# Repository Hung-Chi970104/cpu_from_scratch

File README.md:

## Hardware Specifications & Bill of Materials (BOM)
*** Sry this board is still in production but I'll reship it once it's delivered!!!

This project is inspired by Hyperspace Pirate: https://youtu.be/X31B1pVow1o?si=pDOqtu37fK6EBQ2z

This DIY 4-but CPU uses BJT logic to build various logic gates, while using discrete NPN transistors as saturated switches

| Component Class | Specification / Part Number | Function |
| --- | --- | --- |
| **Active Switching** | 2N3904 (NPN BJT) | Core logic gates (amplification and switching) |
| **Passive Routing** | Standard Rectifier Diodes | Signal isolation and OR-tie routing |
| **Pull-up/Pull-down** | 10kΩ Resistors | Ensuring definitive HIGH/LOW logic states |
| **Base Biasing** | 4.7kΩ Resistors | Base current limiting to prevent thermal runaway |
| **Current Limiting** | 1kΩ Resistors | Collector current limiting |

---

## Schematic Design

The architecture has both **SUM** and **CARRY (Cout)** logic using fundamental logic gates built from scratch

### Logic Gate Topologies

The computational core relies on three primary gate topologies designed from discrete NPN transistors:

1. **NAND Gate:** Series-connected BJTs requiring all inputs to be HIGH to pull the output LOW
2. **NOR Gate:** Parallel-connected BJTs where any HIGH input pulls the output LOW
3. **XOR Gate:** A composite gate critical for the SUM generation

*Gate Implementation Reference:*

* [XOR Gate Schematic](https://github.com/user-attachments/assets/9e057bf3-4b33-4ee1-a783-3fd075c37234)
* [NOR Gate Schematic](https://github.com/user-attachments/assets/835cebbe-9da9-4931-9af1-0fc856e21aca)
* [NAND Gate Schematic](https://github.com/user-attachments/assets/38a2fae2-0add-45c0-82a7-d2f594ea8222)

---

## Validation Using Truth Table

The circuit has been validated against the standard 1-bit full adder truth table, successfully transitioning between all 8 states cleanly:

| Input A | Input B | Carry In (Cin) | SUM Output | Carry Out (Cout) |
| --- | --- | --- | --- | --- |
| 0 | 0 | 0 | **0** | **0** |
| 0 | 0 | 1 | **1** | **0** |
| 0 | 1 | 0 | **1** | **0** |
| 0 | 1 | 1 | **0** | **1** |
| 1 | 0 | 0 | **1** | **0** |
| 1 | 0 | 1 | **0** | **1** |
| 1 | 1 | 0 | **0** | **1** |
| 1 | 1 | 1 | **1** | **1** |

---

## Technical Challenges

To build this, I was forced to learn many things that I hadn't even seen before, such as truth table and logic gates. Truth table is the foundation of computing logic, while logic gates are the way to implement the the logic

* **Fan-Out Limitations & Signal Integrity:** Driving multiple inputs from a single output stage caused severe voltage drops. This required very careful pull-up and base resistor values to ensure subsequent transistor stages have adequate saturation current without dragging the logic HIGH state into the regions that should be low
* **XOR Current Starvation:** The initial Exclusive-OR (XOR) architecture failed due to a topology that tried to drive two separate transistor bases from a single unbuffered node. And this caused current to split in two parallel streams, preventing either transistor from fully switching

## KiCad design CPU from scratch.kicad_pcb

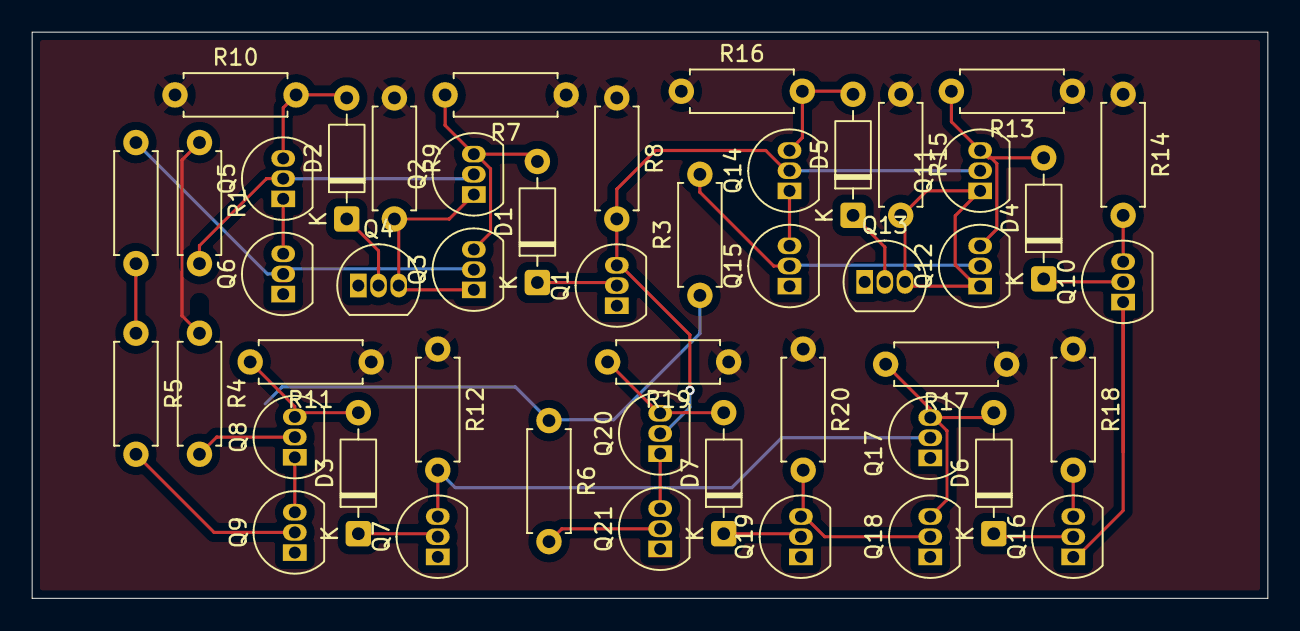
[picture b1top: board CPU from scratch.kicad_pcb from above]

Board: 2 copper layers, 77.8 x 35.6 mm, 48 parts (0 on the bottom side), 36 nets.

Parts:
D1, D2, D3, D4, D5, D6, D7: D; D_DO-35_SOD27_P7.62mm_Horizontal
Q1, Q2, Q3, Q4, Q5, Q6, Q7, Q8, Q9, Q10, Q11, Q12, Q13, Q14, Q15, Q16, Q17, Q18, Q19, Q20, Q21: 2N3904; TO-92_Inline
R1, R2, R3, R4, R5, R6, R7, R8, R9, R10, R11, R12, R13, R14, R15, R16, R17, R18, R19, R20: 1k; R_Axial_DIN0207_L6.3mm_D2.5mm_P7.62mm_Horizontal

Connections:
+5V: R7.1, R8.1, R9.1, R10.1, R11.1, R12.1, R13.1, R14.1, R15.1, R16.1, R17.1, R18.1, R19.1, R20.1
/AND1/In1: Q8.2 (B), R4.2
/AND1/In2: Q9.2 (B), R5.2
/AND1/O: Q7.3 (C), Q17.2 (B), R12.2
/AND2/In1: Q1.3 (C), Q11.2 (B), Q14.2 (B), Q20.2 (B), R8.2
/AND2/In2: Q21.2 (B), R6.2
/AND2/O: Q18.2 (B), Q19.3 (C), R20.2
/XOR1/In1: Q2.2 (B), Q5.2 (B), R1.2
/XOR1/In2: Q3.2 (B), Q6.2 (B), R2.2
/XOR2/In2: Q12.2 (B), Q15.2 (B), R3.2
A: R1.1, R4.1
B: R2.1, R5.1
Cin: R3.1, R6.1
Cout: Q16.3 (C), R18.2
GND: Q1.1 (E), Q4.1 (E), Q6.1 (E), Q7.1 (E), Q9.1 (E), Q10.1 (E), Q13.1 (E), Q15.1 (E), Q16.1 (E), Q17.1 (E), Q18.1 (E), Q19.1 (E), Q21.1 (E)
unnamed: D1.2 (A), Q2.3 (C), Q3.3 (C), R7.2
unnamed: D1.1 (K), Q1.2 (B)
unnamed: D2.2 (A), Q5.3 (C), R10.2
unnamed: D2.1 (K), Q4.2 (B)
unnamed: D3.2 (A), Q8.3 (C), R11.2
unnamed: D3.1 (K), Q7.2 (B)
unnamed: D4.2 (A), Q11.3 (C), Q12.3 (C), R13.2
unnamed: D4.1 (K), Q10.2 (B)
unnamed: D5.2 (A), Q14.3 (C), R16.2
unnamed: D5.1 (K), Q13.2 (B)
unnamed: D6.2 (A), Q17.3 (C), Q18.3 (C), R17.2
unnamed: D6.1 (K), Q16.2 (B)
unnamed: D7.2 (A), Q20.3 (C), R19.2
unnamed: D7.1 (K), Q19.2 (B)
unnamed: Q2.1 (E), Q3.1 (E), Q4.3 (C), R9.2
unnamed: Q5.1 (E), Q6.3 (C)
unnamed: Q8.1 (E), Q9.3 (C)
unnamed: Q11.1 (E), Q12.1 (E), Q13.3 (C), R15.2
unnamed: Q14.1 (E), Q15.3 (C)
unnamed: Q20.1 (E), Q21.3 (C)
S: Q10.3 (C), R14.2

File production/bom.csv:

Designator,Footprint,Quantity,Value,LCSC Part #
"D1_4, D1_3, D1_2, D1, D2_4, D2_3, D2_2, D2, D3_4, D3_3, D3_2, D3, D4_4, D4_3, D4_2, D4, D5_4, D5_3, D5_2, D5, D6_4, D6_3, D6_2, D6, D7_4, D7_3, D7_2, D7",D_DO-35_SOD27_P7.62mm_Horizontal,28,D,
"Q1_4, Q1_3, Q1_2, Q1, Q10_4, Q10_3, Q10_2, Q10, Q11_4, Q11_3, Q11_2, Q11, Q12_4, Q12_3, Q12_2, Q12, Q13_4, Q13_3, Q13_2, Q13, Q14_4, Q14_3, Q14_2, Q14, Q15_4, Q15_3, Q15_2, Q15, Q16_4, Q16_3, Q16_2, Q16, Q17_4, Q17_3, Q17_2, Q17, Q18_4, Q18_3, Q18_2, Q18, Q19_4, Q19_3, Q19_2, Q19, Q2_4, Q2_3, Q2_2, Q2, Q20_4, Q20_3, Q20_2, Q20, Q21_4, Q21_3, Q21_2, Q21, Q3_4, Q3_3, Q3_2, Q3, Q4_4, Q4_3, Q4_2, Q4, Q5_4, Q5_3, Q5_2, Q5, Q6_4, Q6_3, Q6_2, Q6, Q7_4, Q7_3, Q7_2, Q7, Q8_4, Q8_3, Q8_2, Q8, Q9_4, Q9_3, Q9_2, Q9",TO-92_Inline,84,2N3904,
"R1_4, R1_3, R1_2, R1, R10_4, R10_3, R10_2, R10, R11_4, R11_3, R11_2, R11, R12_4, R12_3, R12_2, R12, R13_4, R13_3, R13_2, R13, R14_4, R14_3, R14_2, R14, R15_4, R15_3, R15_2, R15, R16_4, R16_3, R16_2, R16, R17_4, R17_3, R17_2, R17, R18_4, R18_3, R18_2, R18, R19_4, R19_3, R19_2, R19, R2_4, R2_3, R2_2, R2, R20_4, R20_3, R20_2, R20, R3_4, R3_3, R3_2, R3, R4_4, R4_3, R4_2, R4, R5_4, R5_3, R5_2, R5, R6_4, R6_3, R6_2, R6, R7_4, R7_3, R7_2, R7, R8_4, R8_3, R8_2, R8, R9_4, R9_3, R9_2, R9",R_Axial_DIN0207_L6.3mm_D2.5mm_P7.62mm_Horizontal,80,1k,

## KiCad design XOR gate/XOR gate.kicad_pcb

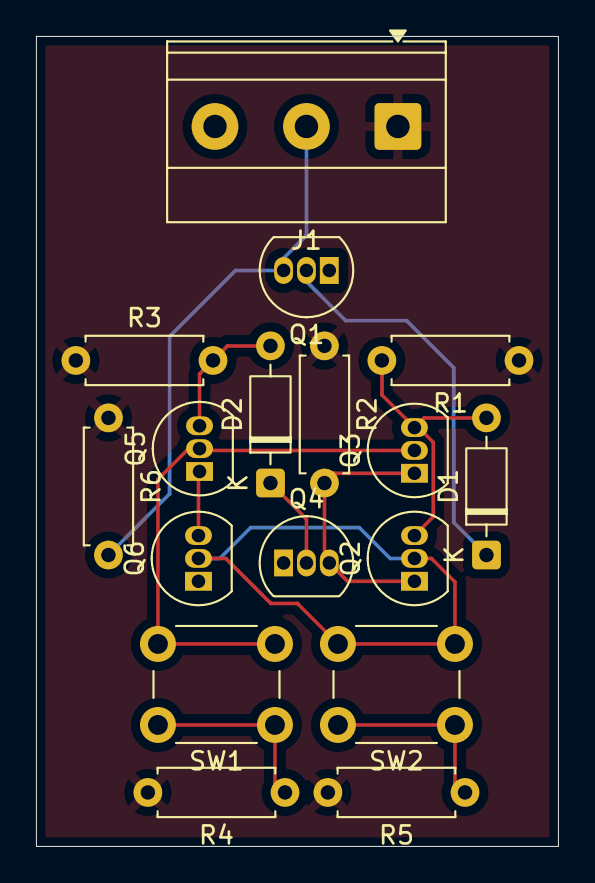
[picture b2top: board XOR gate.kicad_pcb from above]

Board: 2 copper layers, 29.0 x 45.0 mm, 17 parts (0 on the bottom side), 13 nets.

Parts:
D1, D2: D; D_DO-35_SOD27_P7.62mm_Horizontal
J1: Screw_Terminal_01x03; TerminalBlock_Phoenix_MKDS-1,5-3-5.08_1x03_P5.08mm_Horizont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
Q1, Q2, Q3, Q4, Q5, Q6: 2N3904; TO-92_Inline
R1, R2, R3, R4, R5, R6: 1k; R_Axial_DIN0207_L6.3mm_D2.5mm_P7.62mm_Horizontal
SW1, SW2: SW_Push; SW_PUSH_6mm_H4.3mm

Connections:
+5V: J1.1, R1.1, R2.1, R3.1, R4.2, R5.2, R6.1
A: Q3.2 (B), Q5.2 (B), SW1.2
B: Q2.2 (B), Q6.2 (B), SW2.2
GND: J1.3, Q1.1 (E), Q4.1 (E), Q6.1 (E)
unnamed: D1.2 (A), Q2.3 (C), Q3.3 (C), R1.2
unnamed: D1.1 (K), Q1.2 (B)
unnamed: D2.2 (A), Q5.3 (C), R3.2
unnamed: D2.1 (K), Q4.2 (B)
unnamed: Q2.1 (E), Q3.1 (E), Q4.3 (C), R2.2
unnamed: Q5.1 (E), Q6.3 (C)
unnamed: R4.1, SW1.1
unnamed: R5.1, SW2.1
O: J1.2, Q1.3 (C), R6.2

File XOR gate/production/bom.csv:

Designator,Footprint,Quantity,Value,LCSC Part #
"D1, D2",D_DO-35_SOD27_P7.62mm_Horizontal,2,D,
J1,"TerminalBlock_Phoenix_MKDS-1,5-3-5.08_1x03_P5.08mm_Horizontal",1,Screw_Terminal_01x03,
"Q1, Q2, Q3, Q4, Q5, Q6",TO-92_Inline,6,2N3904,
"R1, R2, R3, R4, R5, R6",R_Axial_DIN0207_L6.3mm_D2.5mm_P7.62mm_Horizontal,6,1k,
"SW1, SW2",SW_PUSH_6mm_H4.3mm,2,SW_Push,

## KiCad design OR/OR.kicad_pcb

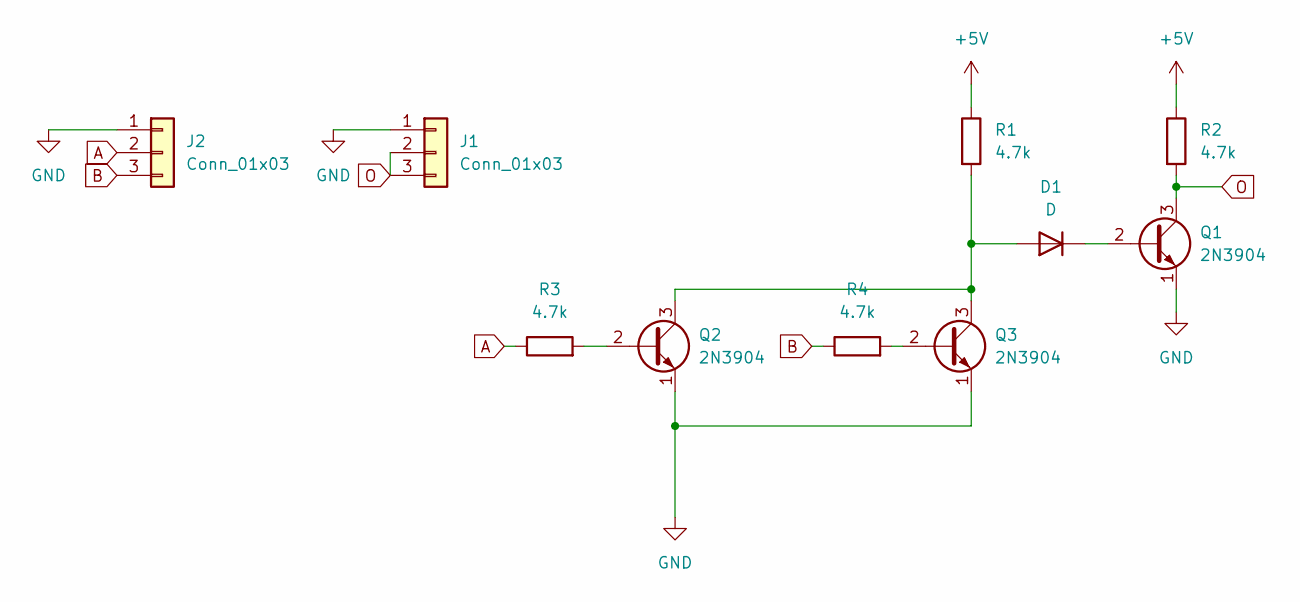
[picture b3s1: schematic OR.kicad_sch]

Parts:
D1: D; D_DO-35_SOD27_P7.62mm_Horizontal
J1, J2: Conn_01x03; PinHeader_1x03_P2.54mm_Vertical
Q1, Q2, Q3: 2N3904; TO-92_Inline
R1, R2, R3, R4: 4.7k; R_Axial_DIN0207_L6.3mm_D2.5mm_P7.62mm_Horizontal

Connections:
+5V: R1.1, R2.1
A: J2.2, R3.1
B: J2.3, R4.1
GND: J1.1, J2.1, Q1.1 (E), Q2.1 (E), Q3.1 (E)
unnamed: D1.2 (A), Q2.3 (C), Q3.3 (C), R1.2
unnamed: D1.1 (K), Q1.2 (B)
unnamed: Q2.2 (B), R3.2
unnamed: Q3.2 (B), R4.2
O: J1.2, J1.3, Q1.3 (C), R2.2

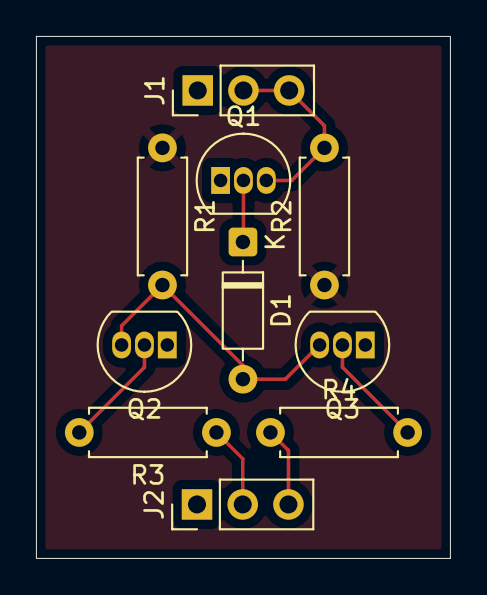
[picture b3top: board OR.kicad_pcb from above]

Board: 2 copper layers, 23.0 x 29.0 mm, 10 parts (0 on the bottom side), 9 nets.

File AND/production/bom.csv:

Designator,Footprint,Quantity,Value,LCSC Part #
D1,D_DO-35_SOD27_P7.62mm_Horizontal,1,D,
"J1, J2",PinHeader_1x03_P2.54mm_Vertical,2,Conn_01x03,
"Q1, Q2, Q3",TO-92_Inline,3,2N3904,
"R1, R2, R3, R4",R_Axial_DIN0207_L6.3mm_D2.5mm_P7.62mm_Horizontal,4,4.7k,

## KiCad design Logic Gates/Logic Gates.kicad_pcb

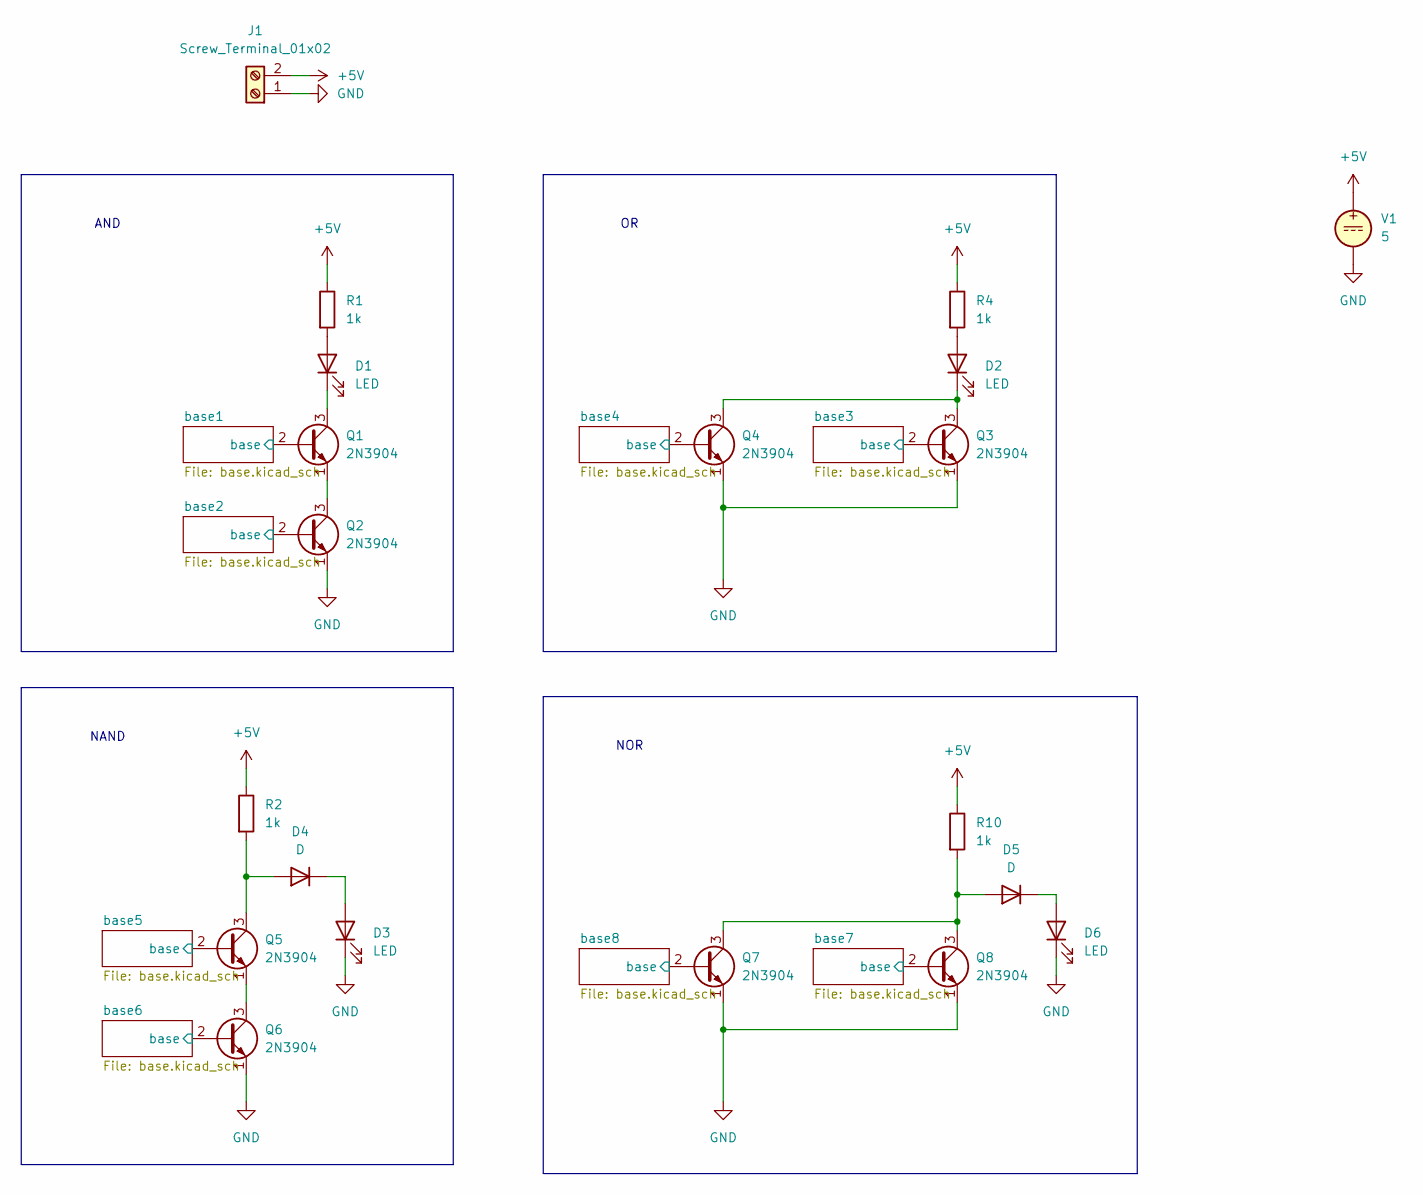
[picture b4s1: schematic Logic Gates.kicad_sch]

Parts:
D1, D2, D3, D6: LED; LED_D3.0mm
D4, D5: D; D_DO-35_SOD27_P7.62mm_Horizontal
J1: Screw_Terminal_01x02; TerminalBlock_Phoenix_MKDS-1,5-2-5.08_1x02_P5.08mm_Horizont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
Q1, Q2, Q3, Q4, Q5, Q6, Q7, Q8: 2N3904; TO-92_Inline
R1, R2, R4, R10: 1k; R_Axial_DIN0207_L6.3mm_D2.5mm_P7.62mm_Horizontal
V1: 5

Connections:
+5V: J1.2, R1.1, R2.1, R4.1, R10.1, V1.1; also elsewhere on the board
/base1/base: Q1.2 (B); also elsewhere on the board
/base2/base: Q2.2 (B); also elsewhere on the board
/base3/base: Q3.2 (B); also elsewhere on the board
/base4/base: Q4.2 (B); also elsewhere on the board
/base5/base: Q5.2 (B); also elsewhere on the board
/base6/base: Q6.2 (B); also elsewhere on the board
/base7/base: Q8.2 (B); also elsewhere on the board
/base8/base: Q7.2 (B); also elsewhere on the board
GND: D3.1 (K), D6.1 (K), J1.1, Q2.1 (E), Q3.1 (E), Q4.1 (E), Q6.1 (E), Q7.1 (E), Q8.1 (E), V1.2
unnamed: D1.2 (A), R1.2
unnamed: D1.1 (K), Q1.3 (C)
unnamed: D2.2 (A), R4.2
unnamed: D2.1 (K), Q3.3 (C), Q4.3 (C)
unnamed: D3.2 (A), D4.1 (K)
unnamed: D4.2 (A), Q5.3 (C), R2.2
unnamed: D5.2 (A), Q7.3 (C), Q8.3 (C), R10.2
unnamed: D5.1 (K), D6.2 (A)
unnamed: Q1.1 (E), Q2.3 (C)
unnamed: Q5.1 (E), Q6.3 (C)

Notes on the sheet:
NAND
NOR
AND

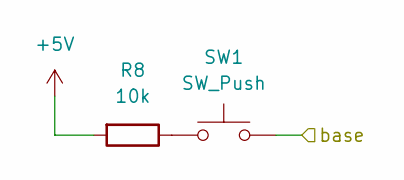
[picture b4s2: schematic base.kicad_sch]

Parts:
R8: 10k; R_Axial_DIN0207_L6.3mm_D2.5mm_P7.62mm_Horizontal
SW1: SW_Push; SW_PUSH_6mm

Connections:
+5V: R8.2; also elsewhere on the board
/base5/base: SW1.2; also elsewhere on the board
unnamed: R8.1, SW1.1

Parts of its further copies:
R3, R5, R6, R7, R9, R11, R12: 10k; R_Axial_DIN0207_L6.3mm_D2.5mm_P7.62mm_Horizontal
SW2, SW3, SW4, SW5, SW6, SW7, SW8: SW_Push; SW_PUSH_6mm

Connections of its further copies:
+5V: R3.2, R5.2, R6.2, R7.2, R9.2, R11.2, R12.2; also elsewhere on the board
/base1/base: SW2.2; also elsewhere on the board
/base2/base: SW3.2; also elsewhere on the board
/base3/base: SW4.2; also elsewhere on the board
/base4/base: SW5.2; also elsewhere on the board
/base6/base: SW6.2; also elsewhere on the board
/base7/base: SW7.2; also elsewhere on the board
/base8/base: SW8.2; also elsewhere on the board
unnamed: R3.1, SW2.1
unnamed: R5.1, SW3.1
unnamed: R6.1, SW4.1
unnamed: R7.1, SW5.1
unnamed: R9.1, SW6.1
unnamed: R11.1, SW7.1
unnamed: R12.1, SW8.1

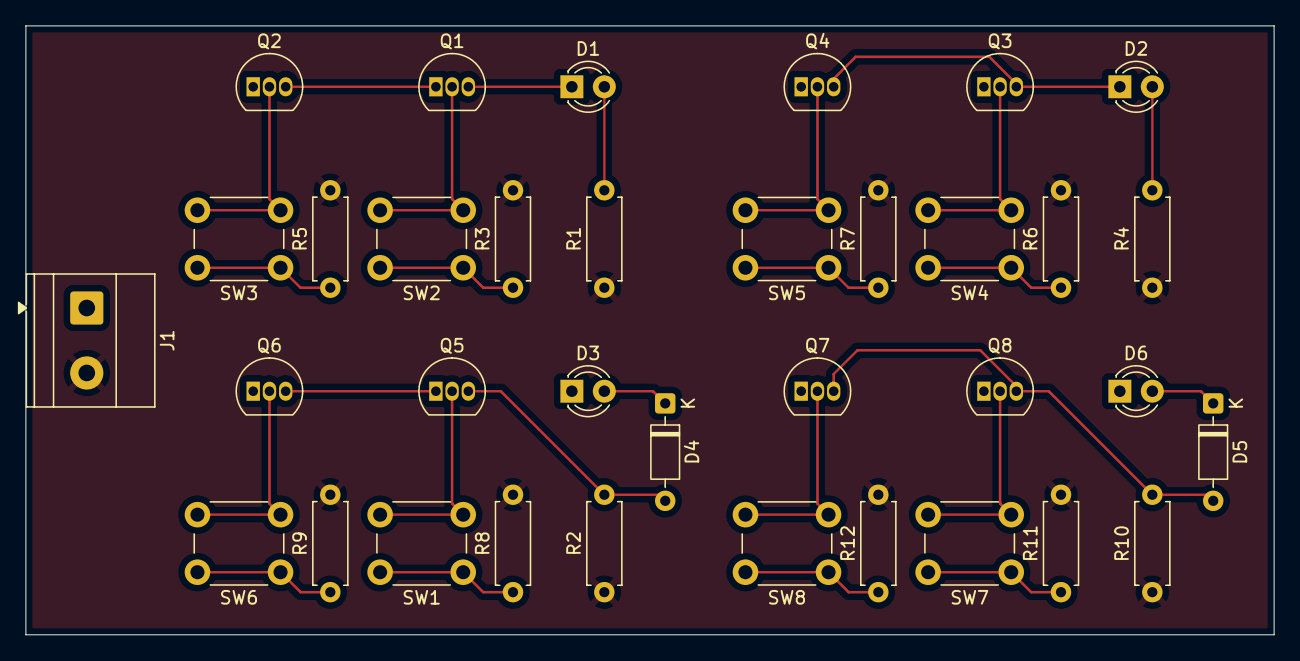
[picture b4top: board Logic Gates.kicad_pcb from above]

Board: 2 copper layers, 97.6 x 47.6 mm, 35 parts (0 on the bottom side), 28 nets.

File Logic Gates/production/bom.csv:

Designator,Footprint,Quantity,Value,LCSC Part #
"D1, D2, D3, D6",LED_D3.0mm,4,LED,
"D4, D5",D_DO-35_SOD27_P7.62mm_Horizontal,2,D,
J1,"TerminalBlock_Phoenix_MKDS-1,5-2-5.08_1x02_P5.08mm_Horizontal",1,Screw_Terminal_01x02,
"Q1, Q2, Q3, Q4, Q5, Q6, Q7, Q8",TO-92_Inline,8,2N3904,
"R1, R10, R2, R4",R_Axial_DIN0207_L6.3mm_D2.5mm_P7.62mm_Horizontal,4,1k,
"R11, R12, R3, R5, R6, R7, R8, R9",R_Axial_DIN0207_L6.3mm_D2.5mm_P7.62mm_Horizontal,8,10k,
"SW1, SW2, SW3, SW4, SW5, SW6, SW7, SW8",SW_PUSH_6mm,8,SW_Push,

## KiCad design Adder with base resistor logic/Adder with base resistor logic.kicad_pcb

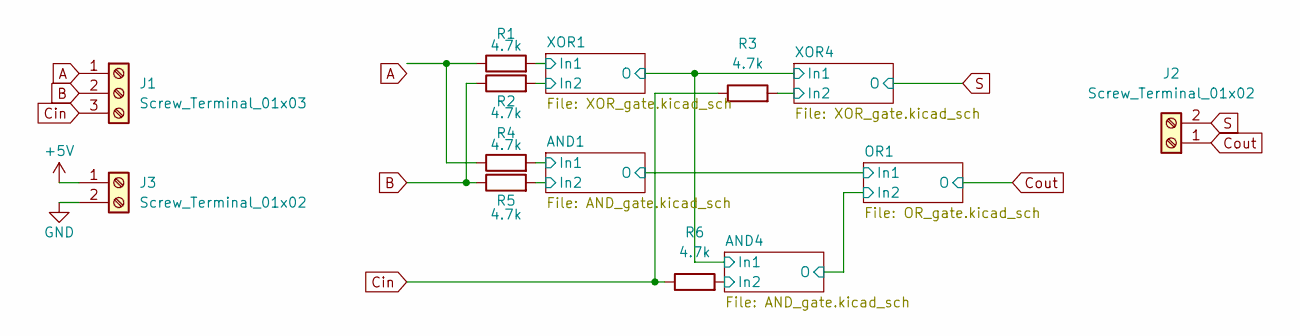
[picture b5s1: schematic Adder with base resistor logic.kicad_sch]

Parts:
J1: Screw_Terminal_01x03; TerminalBlock_Phoenix_MKDS-1,5-3-5.08_1x03_P5.08mm_Horizont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
J2, J3: Screw_Terminal_01x02; TerminalBlock_Phoenix_MKDS-1,5-2-5.08_1x02_P5.08mm_Horizont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
R1, R2, R3, R4, R5, R6: 4.7k; R_Axial_DIN0207_L6.3mm_D2.5mm_P7.62mm_Horizontal

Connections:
+5V: J3.1; also elsewhere on the board
/AND1/In1: R4.2; also elsewhere on the board
/AND1/In2: R5.2; also elsewhere on the board
/AND4/In2: R6.2; also elsewhere on the board
/XOR1/In1: R1.2; also elsewhere on the board
/XOR1/In2: R2.2; also elsewhere on the board
/XOR4/In2: R3.2; also elsewhere on the board
A: J1.1
B: J1.2, R2.1, R5.1
Cin: J1.3, R3.1, R6.1
Cout: J2.1; also elsewhere on the board
GND: J3.2; also elsewhere on the board
unnamed: R1.1, R4.1
S: J2.2; also elsewhere on the board

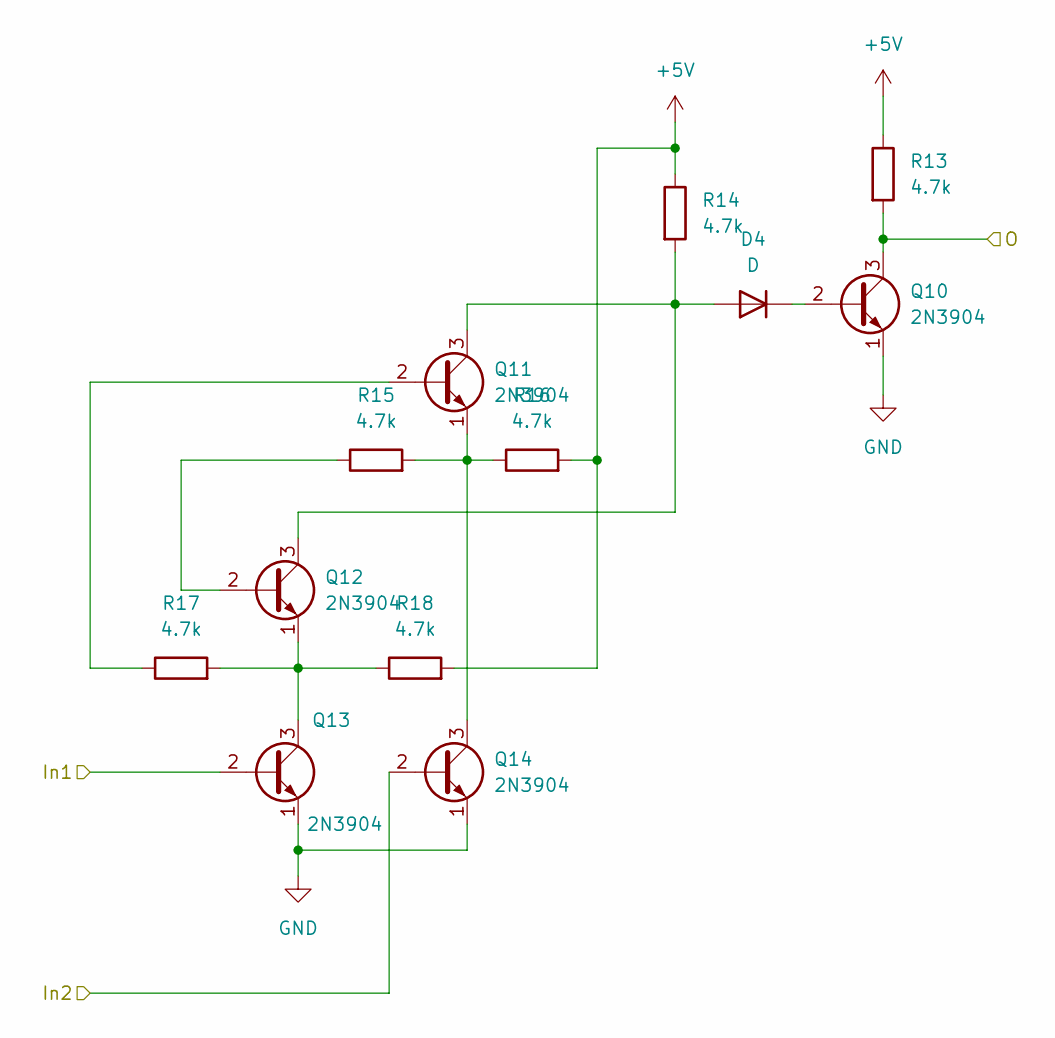
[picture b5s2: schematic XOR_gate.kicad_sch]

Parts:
D4: D; D_DO-35_SOD27_P7.62mm_Horizontal
Q10, Q11, Q12, Q13, Q14: 2N3904; TO-92_Inline
R13, R14, R15, R16, R17, R18: 4.7k; R_Axial_DIN0207_L6.3mm_D2.5mm_P7.62mm_Horizontal

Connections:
+5V: R13.1, R14.1, R16.2, R18.2; also elsewhere on the board
/AND4/In1: Q10.3 (C), R13.2; also elsewhere on the board
/XOR1/In1: Q13.2 (B); also elsewhere on the board
/XOR1/In2: Q14.2 (B); also elsewhere on the board
GND: Q10.1 (E), Q13.1 (E), Q14.1 (E); also elsewhere on the board
unnamed: D4.2 (A), Q11.3 (C), Q12.3 (C), R14.2
unnamed: D4.1 (K), Q10.2 (B)
unnamed: Q11.2 (B), R17.1
unnamed: Q11.1 (E), Q14.3 (C), R15.2, R16.1
unnamed: Q12.2 (B), R15.1
unnamed: Q12.1 (E), Q13.3 (C), R17.2, R18.1

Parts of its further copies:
D5: D; D_DO-35_SOD27_P7.62mm_Horizontal
Q15, Q16, Q17, Q18, Q19: 2N3904; TO-92_Inline
R19, R20, R21, R22, R23, R24: 4.7k; R_Axial_DIN0207_L6.3mm_D2.5mm_P7.62mm_Horizontal

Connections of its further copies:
+5V: R19.1, R20.1, R22.2, R24.2; also elsewhere on the board
/AND4/In1: Q18.2 (B); also elsewhere on the board
/XOR4/In2: Q19.2 (B); also elsewhere on the board
GND: Q15.1 (E), Q18.1 (E), Q19.1 (E); also elsewhere on the board
unnamed: D5.2 (A), Q16.3 (C), Q17.3 (C), R20.2
unnamed: D5.1 (K), Q15.2 (B)
unnamed: Q16.2 (B), R23.1
unnamed: Q16.1 (E), Q19.3 (C), R21.2, R22.1
unnamed: Q17.2 (B), R21.1
unnamed: Q17.1 (E), Q18.3 (C), R23.2, R24.1
S: Q15.3 (C), R19.2; also elsewhere on the board

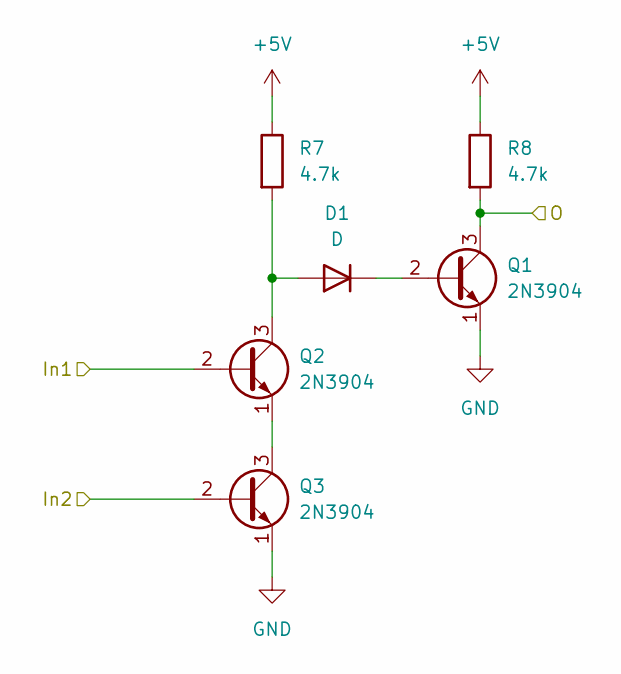
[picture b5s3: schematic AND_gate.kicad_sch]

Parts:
D1: D; D_DO-35_SOD27_P7.62mm_Horizontal
Q1, Q2, Q3: 2N3904; TO-92_Inline
R7, R8: 4.7k; R_Axial_DIN0207_L6.3mm_D2.5mm_P7.62mm_Horizontal

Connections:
+5V: R7.1, R8.1; also elsewhere on the board
/AND1/In1: Q2.2 (B); also elsewhere on the board
/AND1/In2: Q3.2 (B); also elsewhere on the board
/AND1/O: Q1.3 (C), R8.2; also elsewhere on the board
GND: Q1.1 (E), Q3.1 (E); also elsewhere on the board
unnamed: D1.2 (A), Q2.3 (C), R7.2
unnamed: D1.1 (K), Q1.2 (B)
unnamed: Q2.1 (E), Q3.3 (C)

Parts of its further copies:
D2: D; D_DO-35_SOD27_P7.62mm_Horizontal
Q4, Q5, Q6: 2N3904; TO-92_Inline
R9, R10: 4.7k; R_Axial_DIN0207_L6.3mm_D2.5mm_P7.62mm_Horizontal

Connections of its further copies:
+5V: R9.1, R10.1; also elsewhere on the board
/AND4/In1: Q5.2 (B); also elsewhere on the board
/AND4/In2: Q6.2 (B); also elsewhere on the board
/AND4/O: Q4.3 (C), R10.2; also elsewhere on the board
GND: Q4.1 (E), Q6.1 (E); also elsewhere on the board
unnamed: D2.2 (A), Q5.3 (C), R9.2
unnamed: D2.1 (K), Q4.2 (B)
unnamed: Q5.1 (E), Q6.3 (C)

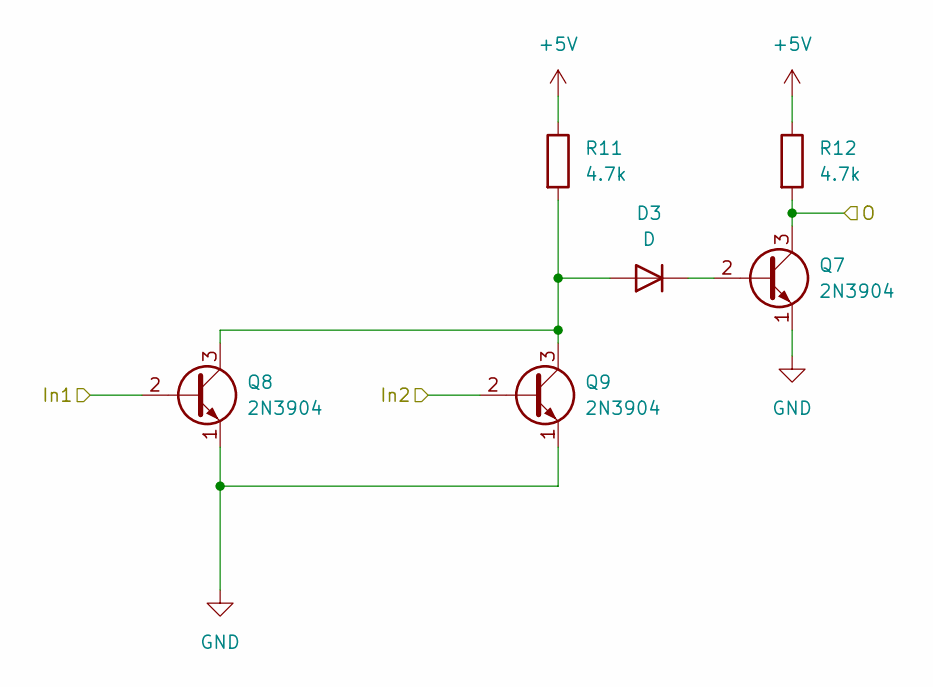
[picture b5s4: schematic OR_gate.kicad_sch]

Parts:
D3: D; D_DO-35_SOD27_P7.62mm_Horizontal
Q7, Q8, Q9: 2N3904; TO-92_Inline
R11, R12: 4.7k; R_Axial_DIN0207_L6.3mm_D2.5mm_P7.62mm_Horizontal

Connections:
+5V: R11.1, R12.1; also elsewhere on the board
/AND1/O: Q8.2 (B); also elsewhere on the board
/AND4/O: Q9.2 (B); also elsewhere on the board
Cout: Q7.3 (C), R12.2; also elsewhere on the board
GND: Q7.1 (E), Q8.1 (E), Q9.1 (E); also elsewhere on the board
unnamed: D3.2 (A), Q8.3 (C), Q9.3 (C), R11.2
unnamed: D3.1 (K), Q7.2 (B)

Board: 2 copper layers, 51 parts (0 on the bottom side), 36 nets, no tracks yet.

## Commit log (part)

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2026-02-20 Readme Update
2026-02-20 Add video link to README
2026-02-22 Fix image link for adder in README
    Updated image link for the adder diagram in README.
2026-03-13 Update PCB
2026-03-14 Enhance README with detailed project information
    Expanded the README to include hardware specifications, logic gate topologies, validation using truth tables, and technical challenges encountered during the project.
2026-03-15 Update Technical Challenges section in README
    Removed the 'Engineering Resolutions' section from the README.
2026-03-17 Update section title from 'Schematic & Architectural Design' to 'Schematic Design'
